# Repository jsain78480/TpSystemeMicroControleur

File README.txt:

# TpSystemeMicroControleur Hicham IDIR et Julien SAINT-LEGER
Ce GITHUB est utilisé pour un TP Systèmes à Microcontroleurs à l'ENSEA.
Il est réalisé en binôme sur 4 séance.
L'objectif de ce TP est de concevoir, assembler et tester une carte électronique contenant un microcontrôleur STM32.
KICAD sera utilisé.
Faire un filtre numérique simple pour prouver le bon fonctionnement de la carte.

Question 1.1.6 : Baud rate 115 200 Bits/s

Question 1.2.13 : PB9 est relié à la masse pour permettre le démarrage du STM32 depuis sa mémoire flash. Si PB9 était connecté à VDD alors le microcontroleur démarrerait en mode programmation. On peut retrouver ces informations dans la datasheet du STM32 ( 3.4.4 At startup, BOOT0 pin and nBOOT0, nBOOT1 and nBOOT_SEL option bits are used to select one of three boot options:• Boot from Flash memory• Boot from System memory• Boot from embedded RAM)

Question 1.2.14 : Les composants L1,C5 et C7 permettent de stabiliser l'alimentation  du STM32.

Question 1.3.3 : Page 3 sur 17 avec un minimum de 0,47 uF et maximum de 1uF (choix pris en conception)

Question 1.3.5 : Page 25 sur 49 où est indiqué que C1 = 10uF et C2 = 0,1uF

Question 1.3.6 : La broche CS/ permet au STM32 de sélectionner le DAC parmis tous les composants utilisés dans notre architecture. On peut voir sur STM32cubeMX que la sortie PA3 est utilisé en GPIO pour venir piloter cette broche. Lorsque CS/=0 alors le DAC est prêt à recevoir des données car il a été selectionné par le STM32.

Question 1.3.7 : Lorsque l'on n'utilise pas la broche LDAC/ alors on est en mode asynchrone, les valeurs analogiques sont placés instantanémment en sortie du DAC et transmis en DAC_OUT. Si on utilise la broche LDAC/ alors on est en mode synchrone, les valeurs analogiques sont placés en sortie du DAC lorsque l'on aura LDAC/=0

Question 1.3.8 : Le signal MISO n'est pas utilisé. Ce qui nous interesse dans notre application c'est la transmission de données du maitre vers l'esclave (STM32 vers le DAC) et non l'inverse. On utilisera dans notre projet le signal MOSI.

Question 1.3.10 : On peut retrouver ces indications dans la datasheet du STM32-V3MINI à la page 19/28

Question 1.4.3 : Par exemple dans 0805, 08 représente la longueur du composant et 05 la largeur du composant (0.08 pouces et 0.05 pouces). Les composants sont des composants CMS. Les empruntes permettent de garantir que les pads seront de la bonne dimension pour placer les composants.

Question 1.4.4 : Ils désignent tous des boitiers utilisés pour entourer les composants placés sur notre PCB. LQFP (Low-profile Quad Flat Package) signifie que c'est un boitier de faible hauteur pouvant couvrir des composants avec de nombreuses broches dissimulés sur les 4 extrémités du composants. SOT-223 est utilisé pour les régulateurs de tensions. A ce stade, nous pouvons penser qu'il sera utilisé pour notre régulateur BU33SD5WG-TR. SOIC est un boitier rectangulaire principalement utilisé pour des composants comme le DAC. A ce stade, nous pouvons penser qu'il sera utilisé pour notre DAC MCP4801-E/SN
test

Question 3.1.2 Utiliser des LL au lieu des HAL permet d'utiliser des registres de bas niveau pour avoir une meilleure optimisation. Les pilotes LL sont spécifiques au microp et les fonctions HAL sont plus portables.

Question 3.1.4 STATIC_INLINE est utilisé pour déclarer une fonction spécifique.

Question 3.1.5 Le compilateur va insérer les fonctions INLINE au besoin d'appel. C'est pour cette raison que du code est écrit dans ces dernières. Cela remplace un appel de fonction communémement réalisé en C.

Question 3.2.2 Nous avons une horloge de 16 Mhz, on aura donc un prescaler=63 sachant que notre Counter period (ARR)=255 pour avoir 1khz.

Question 3.3.3 Nous avons une horloge de 16 Mhz, on aura donc un prescaler=63 sachant que notre Counter period (ARR)=255 pour avoir 1khz.

Question 3.3.6 La routine du service d'interruption se situe dans le fichier stm32l0xx_it.c

Question 3.3.7 Les librairies LL sont beaucoup plus bas niveau et jouent sur les registres. Il est nécessaire de connaître le hardware pour les utiliser. Par soucis de mémoire interne au STM32,leur utilisation est rendu obligatoire pour ce TP. 
              
Question 3.3.8 Il faut gérer le flag dans l'interruption. Si ce n'est pas fait celà on peut boucler en continu dans l'interruption sans y sortir.

Question 3.3.9 Il faut mettre à 0 le flag à la fin de l'interruption. Dans notre cas; nous avons mis LL_TIM_ClearFlag_UPDATE(TIM21)

Question 3.4.5 Il manque le & devant ch dans SerialTransmit(ch,1)

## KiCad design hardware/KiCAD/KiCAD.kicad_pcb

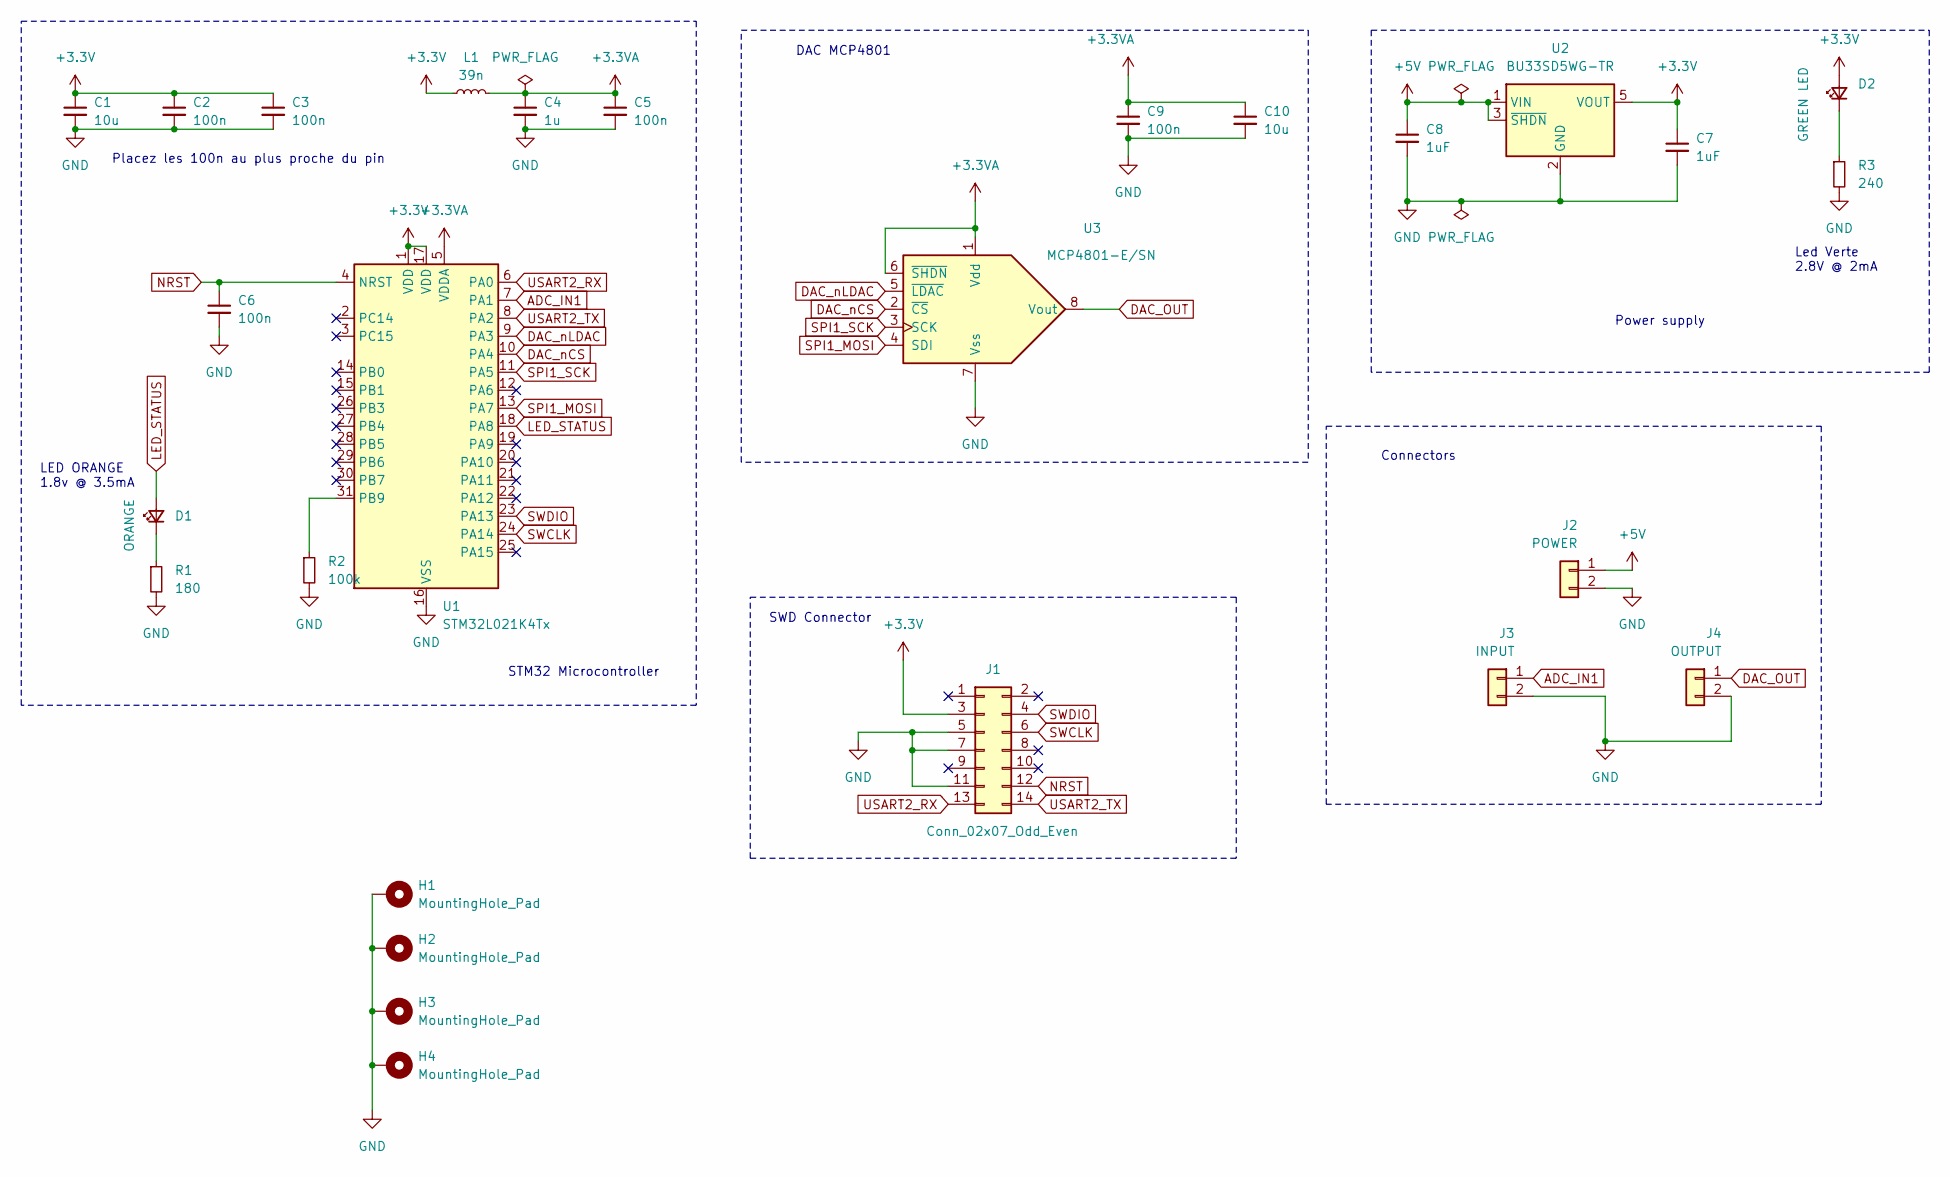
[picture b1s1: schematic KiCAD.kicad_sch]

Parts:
C1, C10: 10u; C_0805_2012Metric_Pad1.18x1.45mm_HandSolder
C2, C3, C5, C6, C9: 100n; C_0805_2012Metric_Pad1.18x1.45mm_HandSolder
C4: 1u; C_0805_2012Metric_Pad1.18x1.45mm_HandSolder
C7, C8: 1uF; C_0805_2012Metric_Pad1.18x1.45mm_HandSolder
D1: ORANGE; LED_0603_1608Metric_Pad1.05x0.95mm_HandSolder
D2: GREEN LED; LED_0603_1608Metric_Pad1.05x0.95mm_HandSolder; MPN 150060GS75000
H1, H2, H3, H4: MountingHole_Pad; MountingHole_3.2mm_M3_Pad
J1: Conn_02x07_Odd_Even; PinHeader_2x07_P1.27mm_Vertical_SMD
J2: POWER; JST_XH_B2B-XH-A_1x02_P2.50mm_Vertical
J3: INPUT; JST_XH_B2B-XH-A_1x02_P2.50mm_Vertical
J4: OUTPUT; JST_XH_B2B-XH-A_1x02_P2.50mm_Vertical
L1: 39n; L_0805_2012Metric_Pad1.05x1.20mm_HandSolder
R1: 180; R_0805_2012Metric_Pad1.20x1.40mm_HandSolder
R2: 100k; R_0805_2012Metric_Pad1.20x1.40mm_HandSolder
R3: 240; R_0805_2012Metric_Pad1.20x1.40mm_HandSolder
U1: STM32L021K4Tx; LQFP-32_7x7mm_P0.8mm
U2: BU33SD5WG-TR; SOT-23-5; MPN BU33SD5WG-TR
U3: MCP4801-E/SN; SOIC-8_3.9x4.9mm_P1.27mm; MPN MCP4801-E/SN

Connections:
+3.3V: C1.1, C2.1, C3.1, C7.1, D2.2 (A), J1.3, L1.1, U1.1 (VDD), U1.17 (VDD), U2.5 (VOUT)
+3.3VA: C4.1, C5.1, C9.1, C10.1, L1.2, U1.5 (VDDA), U3.1 (Vdd), U3.6 (~SHDN)
+5V: C8.1, J2.1, U2.1 (VIN), U2.3 (~SHDN)
ADC_IN1: J3.1, U1.7 (PA1)
DAC_OUT: J4.1, U3.8 (Vout)
DAC_nCS: U1.10 (PA4), U3.2 (~CS)
DAC_nLDAC: U1.9 (PA3), U3.5 (~LDAC)
GND: C1.2, C2.2, C3.2, C4.2, C5.2, C6.2, C7.2, C8.2, C9.2, C10.2, H1.1, H2.1, H3.1, H4.1, J1.5, J1.7, J1.11, J2.2, J3.2, J4.2, R1.2, R2.2, R3.2, U1.16 (VSS), U1.32 (VSS), U2.2 (GND), U3.7 (Vss)
LED_STATUS: D1.2 (A), U1.18 (PA8)
NRST: C6.1, J1.12, U1.4 (NRST)
unnamed: D1.1 (K), R1.1
unnamed: D2.1 (K), R3.1
unnamed: R2.1, U1.31 (PB9)
SPI1_MOSI: U1.13 (PA7), U3.4 (SDI)
SPI1_SCK: U1.11 (PA5), U3.3 (SCK)
SWCLK: J1.6, U1.24 (PA14)
SWDIO: J1.4, U1.23 (PA13)
USART2_RX: J1.13, U1.6 (PA0)
USART2_TX: J1.14, U1.8 (PA2)

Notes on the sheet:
Placez les 100n au plus proche du pin
Connectors
SWD Connector
LED ORANGE 1.8v @ 3.5mA
Led Verte 2.8V @ 2mA
DAC MCP4801
Power supply
STM32 Microcontroller

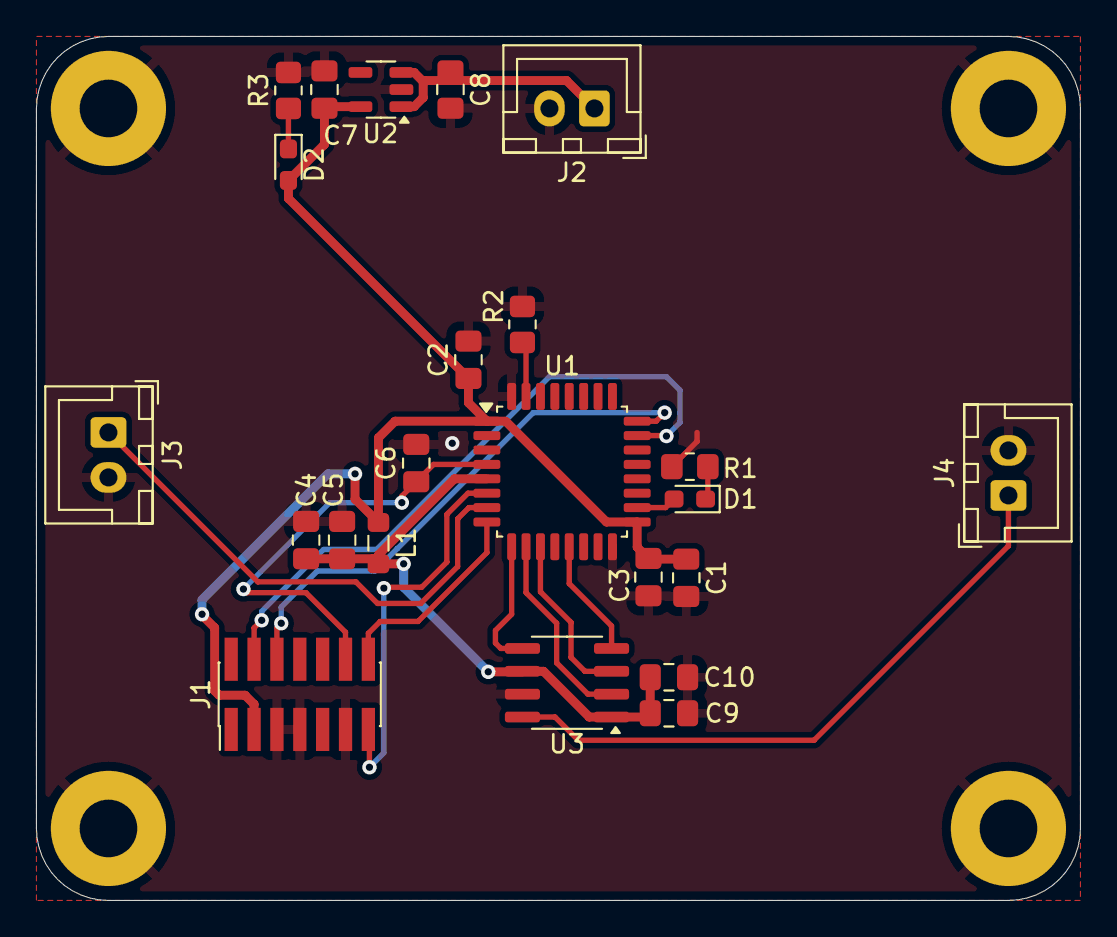
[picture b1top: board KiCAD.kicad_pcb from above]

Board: 2 copper layers, 58.0 x 48.0 mm, 27 parts (0 on the bottom side), 19 nets.

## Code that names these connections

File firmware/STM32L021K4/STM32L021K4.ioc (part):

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Mcu.Name=STM32L021K4Tx
Mcu.Package=LQFP32
Mcu.UserName=STM32L021K4Tx
PA0-CK_IN.Mode=Asynchronous
PA0-CK_IN.Signal=USART2_RX
PA1.Mode=IN1
PA1.Signal=ADC_IN1
PA13.Mode=Serial_Wire
PA13.Signal=SYS_SWDIO
PA14.Mode=Serial_Wire
PA14.Signal=SYS_SWCLK
PA2.Mode=Asynchronous
PA2.Signal=USART2_TX
PA3.GPIOParameters=GPIO_Label
PA3.GPIO_Label=DAC_nLDAC
PA3.Signal=GPIO_Analog
PA4.GPIOParameters=GPIO_Label
PA4.GPIO_Label=DAC_nCS
PA4.Signal=GPIO_Analog
PA5.Mode=Full_Duplex_Master
PA5.Signal=SPI1_SCK
PA6.Mode=Full_Duplex_Master
PA6.Signal=SPI1_MISO
PA7.Mode=Full_Duplex_Master
PA7.Signal=SPI1_MOSI
PA8.Signal=S_TIM2_CH1
RCC.HSE_VALUE=8000000
RCC.SYSCLKFreq_VALUE=4194000
board=custom

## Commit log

2024-02-23 First!
2024-02-23 Rename README.md to README.txt
2024-02-23 ajout datasheet
2024-02-23 ajoutDatasheets
2024-02-23 maj_prepaTP
2024-02-27 update2
2024-02-27 update3
2024-02-27 backup
2024-02-27 update4
2024-02-29 bonjour
2024-02-29 bonjourbonjour
2024-02-29 bonjourbonjour2
